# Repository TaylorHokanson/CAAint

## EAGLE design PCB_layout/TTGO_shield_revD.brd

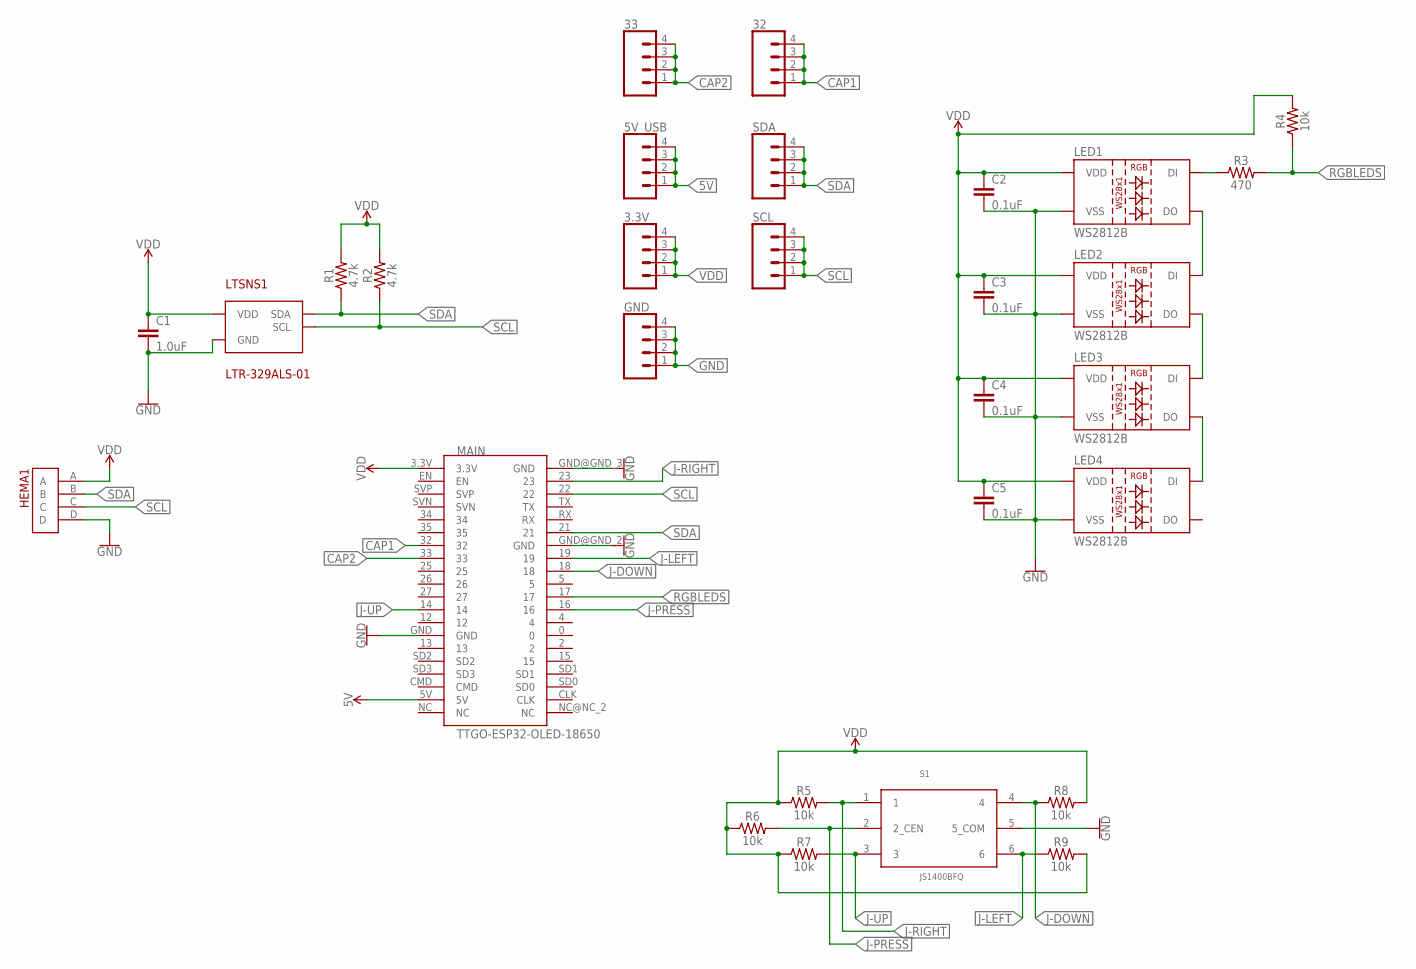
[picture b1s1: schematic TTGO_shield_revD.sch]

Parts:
3.3V, 5V_USB, 32, 33: CONN_041X04_NO_SILK; 1X04_NO_SILK
C1: 1.0uF; 0805
C2, C3, C4, C5: 0.1uF; 0603
GND: CONN_041X04_NO_SILK; 1X04_NO_SILK
HEMA1: 10120045-400LF
LED1, LED2, LED3, LED4: WS2812B
LTSNS1: LTR-329ALS-01; CHIPLED-4
MAIN: TTGO-ESP32-OLED-18650
R1, R2: 4.7k; 0603
R3: 470; 0603
R4, R5, R6, R7, R8, R9: 10k; 0603
S1: JS1400BFQ
SCL: CONN_041X04_NO_SILK; 1X04_NO_SILK
SDA: CONN_041X04_NO_SILK; 1X04_NO_SILK

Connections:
5V: 5V_USB.1, 5V_USB.2, 5V_USB.3, 5V_USB.4, MAIN.5V
CAP1: 32.1, 32.2, 32.3, 32.4, MAIN.32
CAP2: 33.1, 33.2, 33.3, 33.4, MAIN.33
GND: C1.2, C2.2, C3.2, C4.2, C5.2, GND.1, GND.2, GND.3, GND.4, HEMA1.D, LED1.3 (VSS), LED2.3 (VSS), LED3.3 (VSS), LED4.3 (VSS), LTSNS1.2 (GND), MAIN.GND, MAIN.GND@GND_2 (GND), MAIN.GND@GND_3 (GND), S1.5 (5_COM)
J-DOWN: MAIN.18, R8.1, S1.4
J-LEFT: MAIN.19, R9.1, S1.6
J-PRESS: MAIN.16, R6.2, S1.2 (2_CEN)
J-RIGHT: MAIN.23, R5.2, S1.1
J-UP: MAIN.14, R7.2, S1.3
unnamed: LED1.2 (DO), LED2.4 (DI)
unnamed: LED2.2 (DO), LED3.4 (DI)
unnamed: LED3.2 (DO), LED4.4 (DI)
unnamed: LED1.4 (DI), R3.1
RGBLEDS: MAIN.17, R3.2, R4.1
SCL: HEMA1.C, LTSNS1.4 (SCL), MAIN.22, R2.1, SCL.1, SCL.2, SCL.3, SCL.4
SDA: HEMA1.B, LTSNS1.3 (SDA), MAIN.21, R1.1, SDA.1, SDA.2, SDA.3, SDA.4
VDD: 3.3V.1, 3.3V.2, 3.3V.3, 3.3V.4, C1.1, C2.1, C3.1, C4.1, C5.1, HEMA1.A, LED1.1 (VDD), LED2.1 (VDD), LED3.1 (VDD), LED4.1 (VDD), LTSNS1.1 (VDD), MAIN.3.3V, R1.2, R2.2, R4.2, R5.1, R6.1, R7.1, R8.2, R9.2

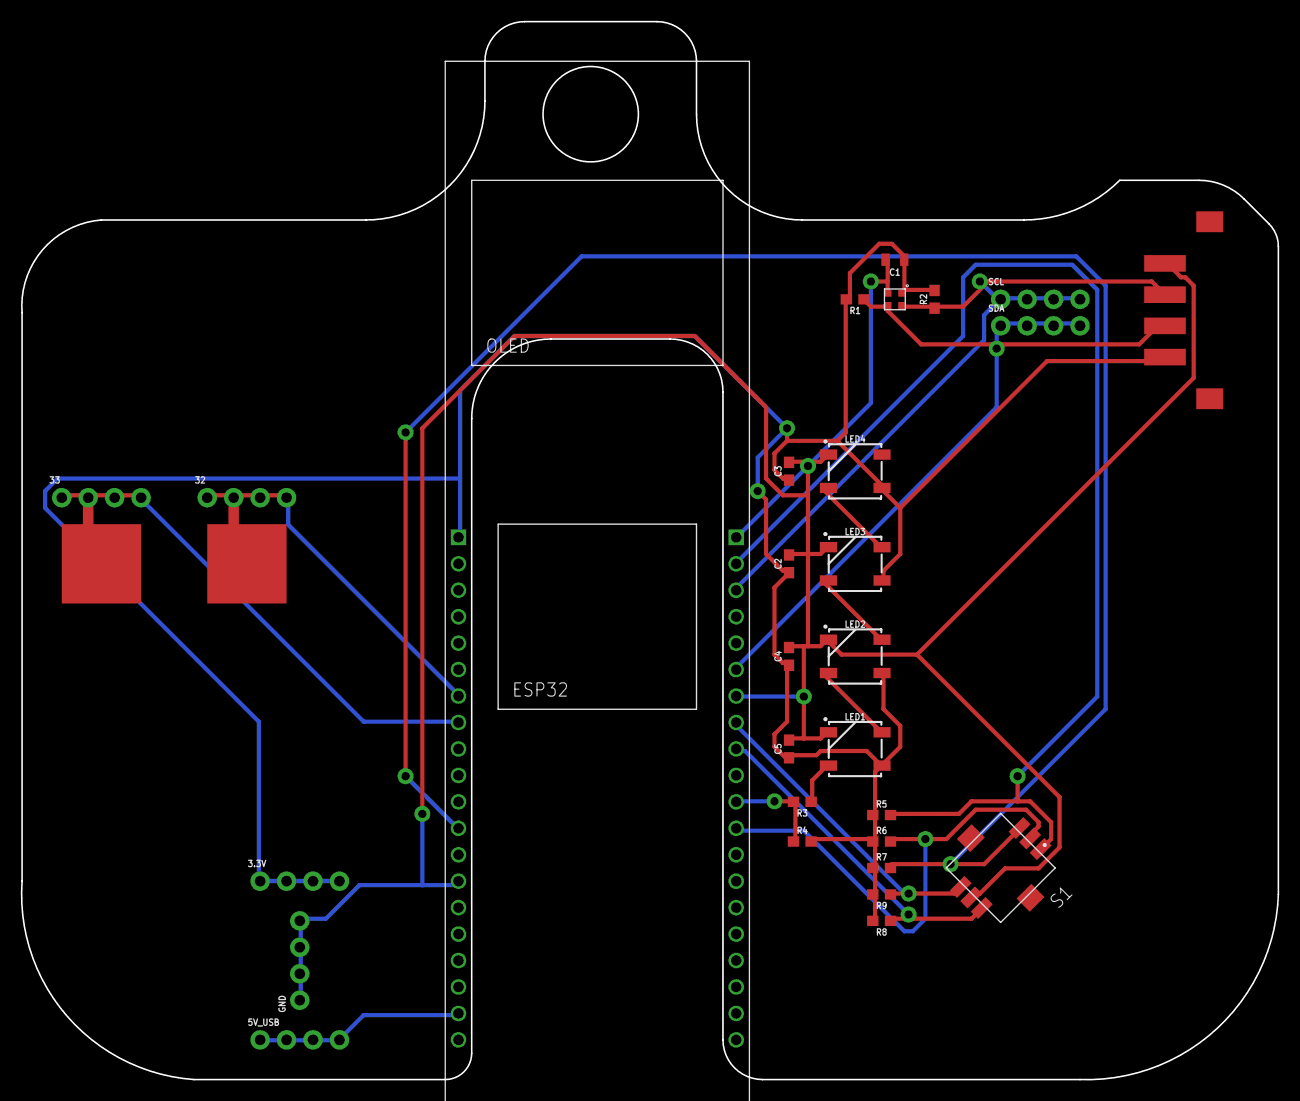
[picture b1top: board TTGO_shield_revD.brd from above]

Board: 2 copper layers, 120.7 x 101.6 mm, 29 parts (0 on the bottom side), 17 nets.

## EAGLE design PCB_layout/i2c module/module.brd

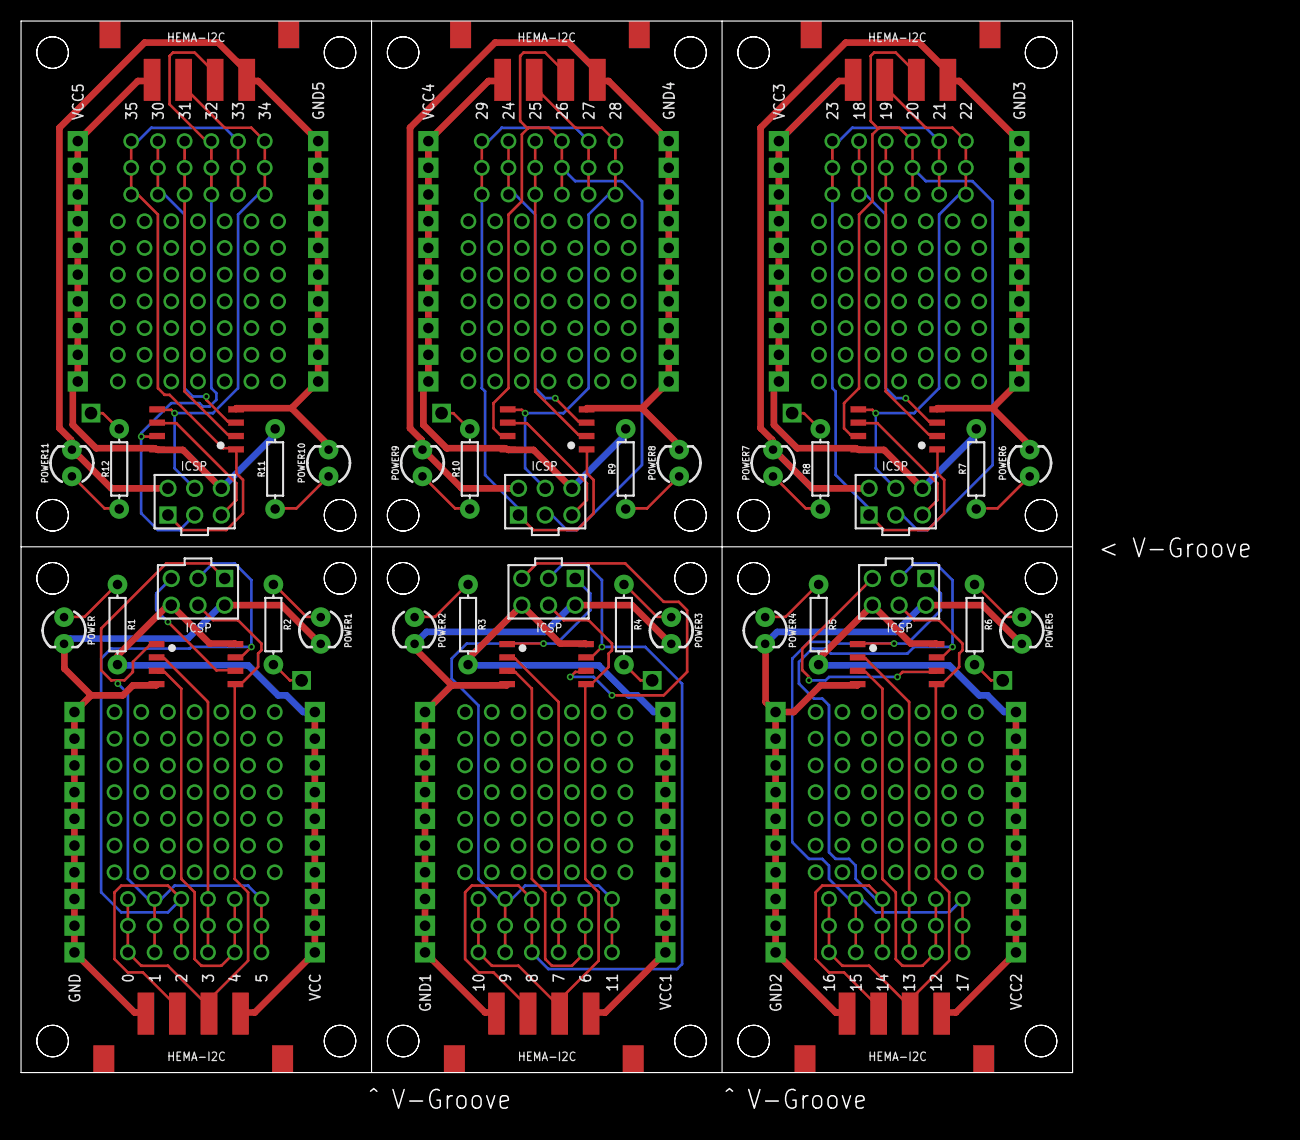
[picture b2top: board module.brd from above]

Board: 2 copper layers, 100.0 x 100.0 mm, 102 parts (0 on the bottom side), 66 nets.

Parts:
0, 1, 2, 3, 4, 5, 6, 7, 8, 9, 10, 11, 12, 13, 14, 15, 16, 17, 18, 19, 20, 21, 22, 23, 24, 25, 26, 27, 28, 29, 30, 31, 32, 33, 34, 35: 3X-PADS-CONNECTED; 3X-PADS
GND, GND1, GND2, GND3, GND4, GND5: 10X-PADS
IC1, IC2, IC3, IC4, IC5, IC6: ATTINY85-20SU; SOT127P798X216-8N
J1, J2, J3, J4, J5, J6: M20-9980346; HDRV6W64P254_2X3_762X508X868P
P1, P2, P3, P4, P5, P6: PROTO_VIAS_01X01-1.2; PROTO_VIAS_01X01_1.2
POWER, POWER1, POWER2, POWER3, POWER4, POWER5, POWER6, POWER7, POWER8, POWER9, POWER10, POWER11: LED_3MM
R1, R2, R3, R4, R5, R6, R7, R8, R9, R10, R11, R12: 220; AXIAL-0.3
U$1, U$3, U$5, U$7, U$9, U$11: HEMA-I2C
U$2, U$4, U$6, U$8, U$10, U$12: 7X-PADS-NC
VCC, VCC1, VCC2, VCC3, VCC4, VCC5: 10X-PADS

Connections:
GND: GND.P$1, GND.P$2, GND.P$3, GND.P$4, GND.P$5, GND.P$6, GND.P$7, GND.P$8, GND.P$9, GND.P$10, IC1.GND, J1.GND, POWER.K, POWER1.K, U$1.A
GND1: GND1.P$1, GND1.P$2, GND1.P$3, GND1.P$4, GND1.P$5, GND1.P$6, GND1.P$7, GND1.P$8, GND1.P$9, GND1.P$10, IC2.GND, J2.GND, POWER2.K, POWER3.K, U$3.A
GND2: GND2.P$1, GND2.P$2, GND2.P$3, GND2.P$4, GND2.P$5, GND2.P$6, GND2.P$7, GND2.P$8, GND2.P$9, GND2.P$10, IC3.GND, J3.GND, POWER4.K, POWER5.K, U$5.A
GND3: GND3.P$1, GND3.P$2, GND3.P$3, GND3.P$4, GND3.P$5, GND3.P$6, GND3.P$7, GND3.P$8, GND3.P$9, GND3.P$10, IC4.GND, J4.GND, POWER6.K, POWER7.K, U$7.A
GND4: GND4.P$1, GND4.P$2, GND4.P$3, GND4.P$4, GND4.P$5, GND4.P$6, GND4.P$7, GND4.P$8, GND4.P$9, GND4.P$10, IC5.GND, J5.GND, POWER8.K, POWER9.K, U$9.A
GND5: GND5.P$1, GND5.P$2, GND5.P$3, GND5.P$4, GND5.P$5, GND5.P$6, GND5.P$7, GND5.P$8, GND5.P$9, GND5.P$10, IC6.GND, J6.GND, POWER10.K, POWER11.K, U$11.A
unnamed: POWER1.A, R2.P$1
unnamed: P1.1, R2.P$2
unnamed: POWER2.A, R3.P$1
unnamed: POWER3.A, R4.P$1
unnamed: P2.1, R4.P$2
unnamed: POWER4.A, R5.P$1
unnamed: POWER5.A, R6.P$1
unnamed: P3.1, R6.P$2
unnamed: POWER6.A, R7.P$1
unnamed: POWER7.A, R8.P$1
unnamed: POWER.A, R1.P$1
unnamed: P4.1, R8.P$2
unnamed: POWER8.A, R9.P$1
unnamed: POWER9.A, R10.P$1
unnamed: P5.1, R10.P$2
unnamed: POWER10.A, R11.P$1
unnamed: POWER11.A, R12.P$1
unnamed: P6.1, R12.P$2
PB0: 0.P$1, 0.P$2, 0.P$3, IC1.PB0, J1.PB0, U$1.C
PB1: IC1.PB1, J1.PB1
PB2: 2.P$1, 2.P$2, 2.P$3, IC1.PB2, J1.PB2, U$1.B
PB3: 3.P$1, 3.P$2, 3.P$3, IC1.PB3
PB4: 4.P$1, 4.P$2, 4.P$3, IC1.PB4
PB5: 1.P$1, 1.P$2, 1.P$3, 5.P$1, 5.P$2, 5.P$3, IC1.PB5, J1.PB5
PB6: 10.P$1, 10.P$2, 10.P$3, IC2.PB0, J2.PB0, U$3.C
PB7: 7.P$1, 7.P$2, 7.P$3, IC2.PB3
PB8: 6.P$1, 6.P$2, 6.P$3, IC2.PB4
PB9: 8.P$1, 8.P$2, 8.P$3, IC2.PB2, J2.PB2, U$3.B
PB10: 9.P$1, 9.P$2, 9.P$3, 11.P$1, 11.P$2, 11.P$3, IC2.PB5, J2.PB5
PB11: IC2.PB1, J2.PB1
PB12: 16.P$1, 16.P$2, 16.P$3, IC3.PB0, J3.PB0, U$5.C
PB13: 13.P$1, 13.P$2, 13.P$3, IC3.PB3
PB14: 12.P$1, 12.P$2, 12.P$3, IC3.PB4
PB15: 14.P$1, 14.P$2, 14.P$3, IC3.PB2, J3.PB2, U$5.B
PB16: 15.P$1, 15.P$2, 15.P$3, 17.P$1, 17.P$2, 17.P$3, IC3.PB5, J3.PB5
PB17: IC3.PB1, J3.PB1
PB18: 22.P$1, 22.P$2, 22.P$3, IC4.PB0, J4.PB0, U$7.C
PB19: 19.P$1, 19.P$2, 19.P$3, IC4.PB3
PB20: 18.P$1, 18.P$2, 18.P$3, IC4.PB4
PB21: 20.P$1, 20.P$2, 20.P$3, IC4.PB2, J4.PB2, U$7.B
PB22: 21.P$1, 21.P$2, 21.P$3, 23.P$1, 23.P$2, 23.P$3, IC4.PB5, J4.PB5
PB23: IC4.PB1, J4.PB1
PB24: 28.P$1, 28.P$2, 28.P$3, IC5.PB0, J5.PB0, U$9.C
PB25: 25.P$1, 25.P$2, 25.P$3, IC5.PB3
PB26: 24.P$1, 24.P$2, 24.P$3, IC5.PB4
PB27: 26.P$1, 26.P$2, 26.P$3, IC5.PB2, J5.PB2, U$9.B
PB28: 27.P$1, 27.P$2, 27.P$3, 29.P$1, 29.P$2, 29.P$3, IC5.PB5, J5.PB5
PB29: IC5.PB1, J5.PB1
PB30: 34.P$1, 34.P$2, 34.P$3, IC6.PB0, J6.PB0, U$11.C
PB31: 31.P$1, 31.P$2, 31.P$3, IC6.PB3
PB32: 30.P$1, 30.P$2, 30.P$3, IC6.PB4
PB33: 32.P$1, 32.P$2, 32.P$3, IC6.PB2, J6.PB2, U$11.B
PB34: 33.P$1, 33.P$2, 33.P$3, 35.P$1, 35.P$2, 35.P$3, IC6.PB5, J6.PB5
PB35: IC6.PB1, J6.PB1
VCC: IC1.VCC, J1.VCC, R1.P$2, U$1.D, VCC.P$1, VCC.P$2, VCC.P$3, VCC.P$4, VCC.P$5, VCC.P$6, VCC.P$7, VCC.P$8, VCC.P$9, VCC.P$10
VCC1: IC2.VCC, J2.VCC, R3.P$2, U$3.D, VCC1.P$1, VCC1.P$2, VCC1.P$3, VCC1.P$4, VCC1.P$5, VCC1.P$6, VCC1.P$7, VCC1.P$8, VCC1.P$9, VCC1.P$10
VCC2: IC3.VCC, J3.VCC, R5.P$2, U$5.D, VCC2.P$1, VCC2.P$2, VCC2.P$3, VCC2.P$4, VCC2.P$5, VCC2.P$6, VCC2.P$7, VCC2.P$8, VCC2.P$9, VCC2.P$10
VCC3: IC4.VCC, J4.VCC, R7.P$2, U$7.D, VCC3.P$1, VCC3.P$2, VCC3.P$3, VCC3.P$4, VCC3.P$5, VCC3.P$6, VCC3.P$7, VCC3.P$8, VCC3.P$9, VCC3.P$10
VCC4: IC5.VCC, J5.VCC, R9.P$2, U$9.D, VCC4.P$1, VCC4.P$2, VCC4.P$3, VCC4.P$4, VCC4.P$5, VCC4.P$6, VCC4.P$7, VCC4.P$8, VCC4.P$9, VCC4.P$10
VCC5: IC6.VCC, J6.VCC, R11.P$2, U$11.D, VCC5.P$1, VCC5.P$2, VCC5.P$3, VCC5.P$4, VCC5.P$5, VCC5.P$6, VCC5.P$7, VCC5.P$8, VCC5.P$9, VCC5.P$10

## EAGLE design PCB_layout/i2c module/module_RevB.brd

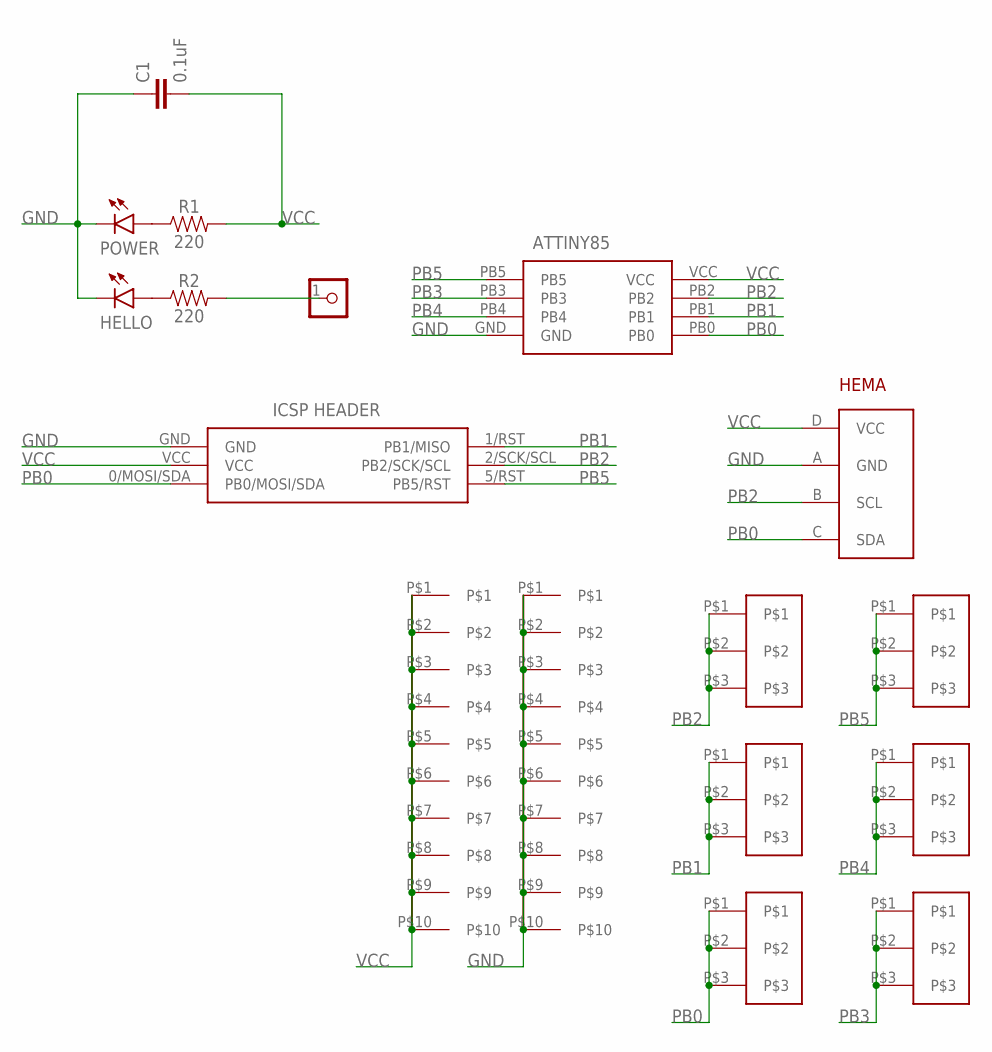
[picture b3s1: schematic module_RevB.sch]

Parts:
0, 1, 2, 3, 4, 5: 3X-PADS-CONNECTED; 3X-PADS
C1: 0.1uF; 0603
GND: 10X-PADS
HELLO: LED3MM
IC1: ATTINY85-20SU; SOT127P798X216-8N
J1: M20-9980346; HDRV6W64P254_2X3_762X508X868P
P1: PROTO_VIAS_01X01-1.2; PROTO_VIAS_01X01_1.2
POWER: LED3MM
R1, R2: 220; AXIAL-0.3
U$1: HEMA-I2C
VCC: 10X-PADS

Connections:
GND: C1.1, GND.P$1, GND.P$2, GND.P$3, GND.P$4, GND.P$5, GND.P$6, GND.P$7, GND.P$8, GND.P$9, GND.P$10, HELLO.NEG, IC1.GND, J1.GND, POWER.NEG, U$1.A (GND)
unnamed: POWER.POS, R1.P$1 (1)
unnamed: P1.1, R2.P$2 (2)
unnamed: HELLO.POS, R2.P$1 (1)
PB0: 0.P$1, 0.P$2, 0.P$3, IC1.PB0, J1.0/MOSI/SDA (PB0/MOSI/SDA), U$1.C (SDA)
PB1: 1.P$1, 1.P$2, 1.P$3, IC1.PB1, J1.1/RST (PB1/MISO)
PB2: 2.P$1, 2.P$2, 2.P$3, IC1.PB2, J1.2/SCK/SCL (PB2/SCK/SCL), U$1.B (SCL)
PB3: 3.P$1, 3.P$2, 3.P$3, IC1.PB3
PB4: 4.P$1, 4.P$2, 4.P$3, IC1.PB4
PB5: 5.P$1, 5.P$2, 5.P$3, IC1.PB5, J1.5/RST (PB5/RST)
VCC: C1.2, IC1.VCC, J1.VCC, R1.P$2 (2), U$1.D (VCC), VCC.P$1, VCC.P$2, VCC.P$3, VCC.P$4, VCC.P$5, VCC.P$6, VCC.P$7, VCC.P$8, VCC.P$9, VCC.P$10

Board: 2 copper layers, 18 parts (0 on the bottom side), 11 nets, no tracks yet.

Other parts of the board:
U$2: 7X-PADS-NC

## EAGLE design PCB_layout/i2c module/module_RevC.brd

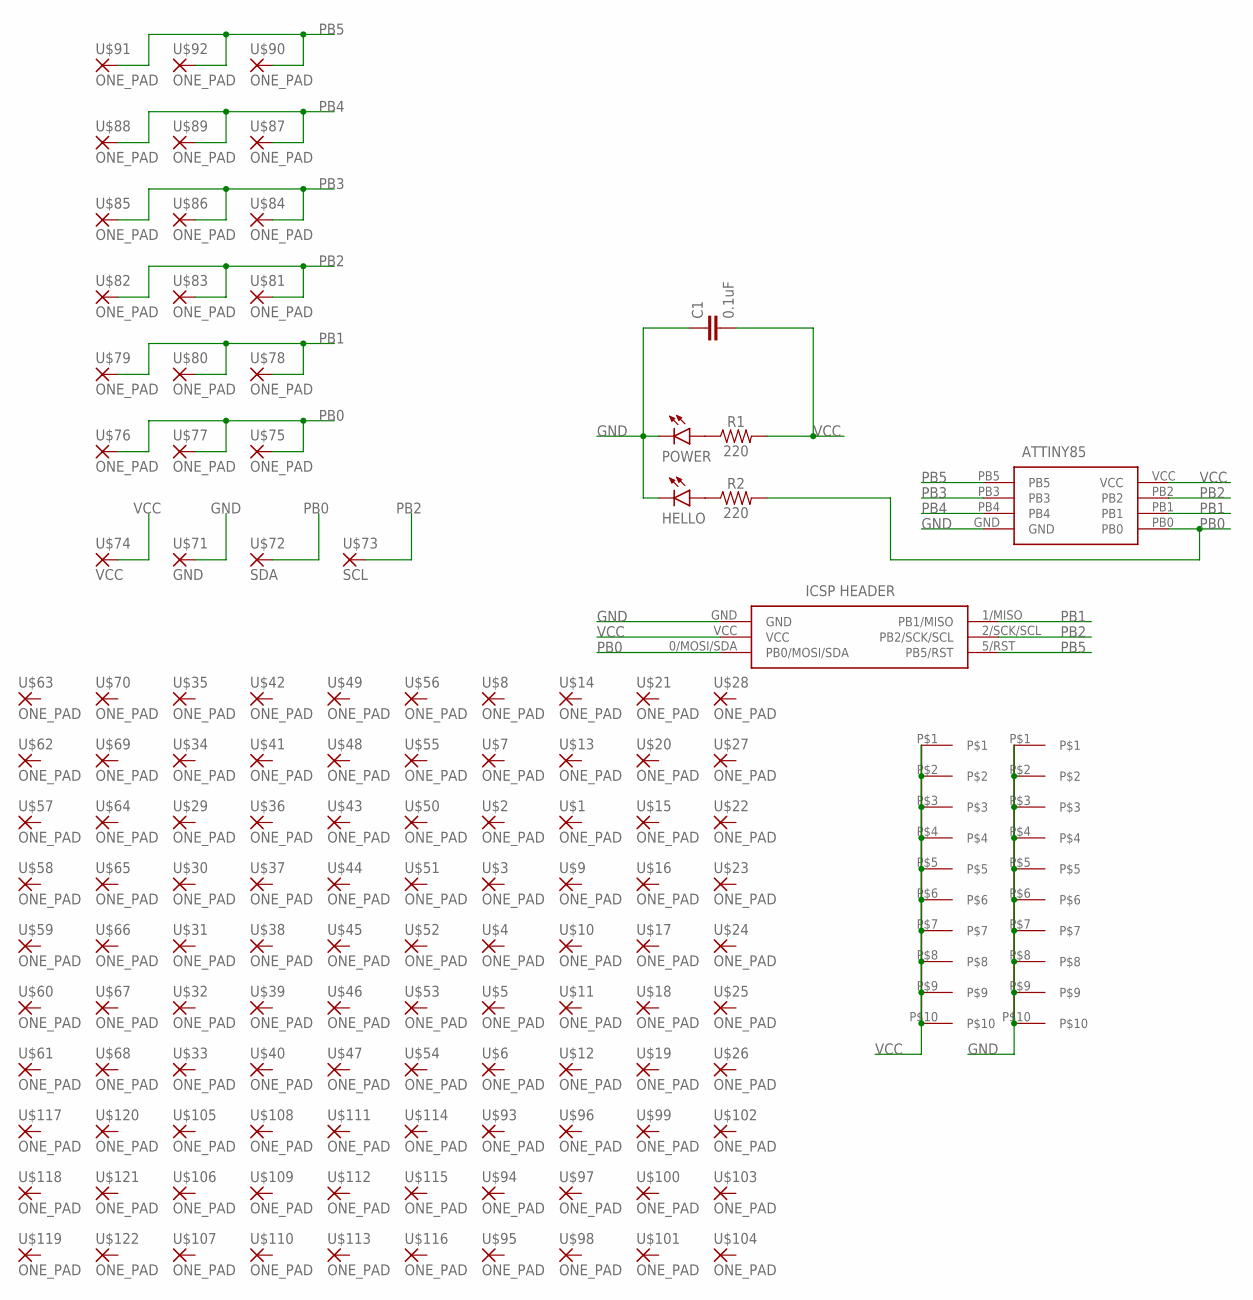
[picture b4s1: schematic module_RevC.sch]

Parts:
C1: 0.1uF; 0603
GND: 10X-PADS
HELLO: LED3MM
IC1: ATTINY85-20SU; SOT127P798X216-8N
J1: M20-9980346; HDRV6W64P254_2X3_762X508X868P
POWER: LED3MM
R1, R2: 220; AXIAL-0.3
U$1, U$2, U$3, U$4, U$5, U$6, U$7, U$8, U$9, U$10, U$11, U$12, U$13, U$14, U$15, U$16, U$17, U$18, U$19, U$20, U$21, U$22, U$23, U$24, U$25, U$26, U$27, U$28, U$29, U$30, U$31, U$32, U$33, U$34, U$35, U$36, U$37, U$38, U$39, U$40, U$41, U$42, U$43, U$44, U$45, U$46, U$47, U$48, U$49, U$50, U$51, U$52, U$53, U$54, U$55, U$56, U$57, U$58, U$59, U$60, U$61, U$62, U$63, U$64, U$65, U$66, U$67, U$68, U$69, U$70, U$75, U$76, U$77, U$78, U$79, U$80, U$81, U$82, U$83, U$84, U$85, U$86, U$87, U$88, U$89, U$90, U$91, U$92, U$93, U$94, U$95, U$96, U$97, U$98, U$99, U$100, U$101, U$102, U$103, U$104, U$105, U$106, U$107, U$108, U$109, U$110, U$111, U$112, U$113, U$114, U$115, U$116, U$117, U$118, U$119, U$120, U$121, U$122: ONE_PAD; 1X01
U$71: GND; 1X01
U$72: SDA; 1X01
U$73: SCL; 1X01
U$74: VCC; 1X01
VCC: 10X-PADS

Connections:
GND: C1.1, GND.P$1, GND.P$2, GND.P$3, GND.P$4, GND.P$5, GND.P$6, GND.P$7, GND.P$8, GND.P$9, GND.P$10, HELLO.NEG, IC1.GND, J1.GND, POWER.NEG, U$71.1
unnamed: POWER.POS, R1.P$1 (1)
unnamed: HELLO.POS, R2.P$1 (1)
PB0: IC1.PB0, J1.0/MOSI/SDA (PB0/MOSI/SDA), R2.P$2 (2), U$72.1, U$75.1, U$76.1, U$77.1
PB1: IC1.PB1, J1.1/MISO (PB1/MISO), U$78.1, U$79.1, U$80.1
PB2: IC1.PB2, J1.2/SCK/SCL (PB2/SCK/SCL), U$73.1, U$81.1, U$82.1, U$83.1
PB3: IC1.PB3, U$84.1, U$85.1, U$86.1
PB4: IC1.PB4, U$87.1, U$88.1, U$89.1
PB5: IC1.PB5, J1.5/RST (PB5/RST), U$90.1, U$91.1, U$92.1
VCC: C1.2, IC1.VCC, J1.VCC, R1.P$2 (2), U$74.1, VCC.P$1, VCC.P$2, VCC.P$3, VCC.P$4, VCC.P$5, VCC.P$6, VCC.P$7, VCC.P$8, VCC.P$9, VCC.P$10

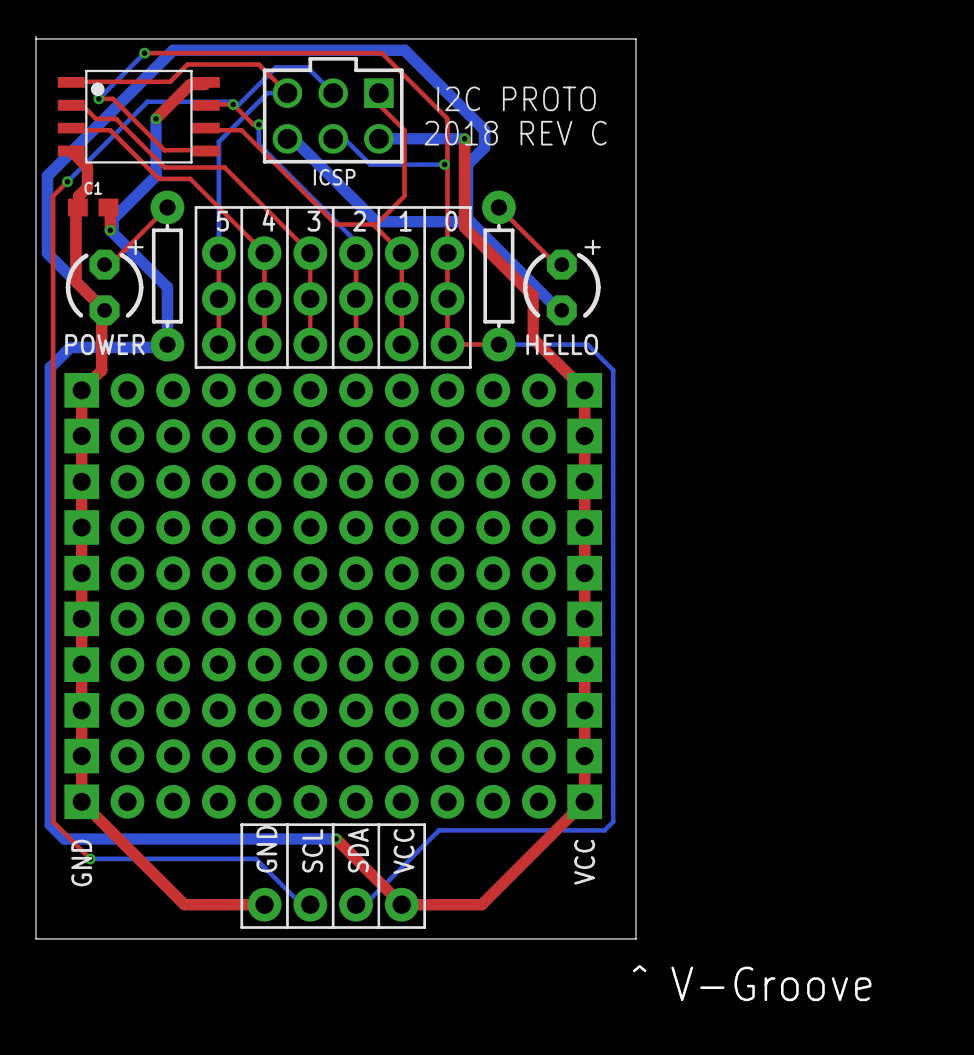
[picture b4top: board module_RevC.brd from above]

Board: 2 copper layers, 33.3 x 50.2 mm, 131 parts (0 on the bottom side), 10 nets.

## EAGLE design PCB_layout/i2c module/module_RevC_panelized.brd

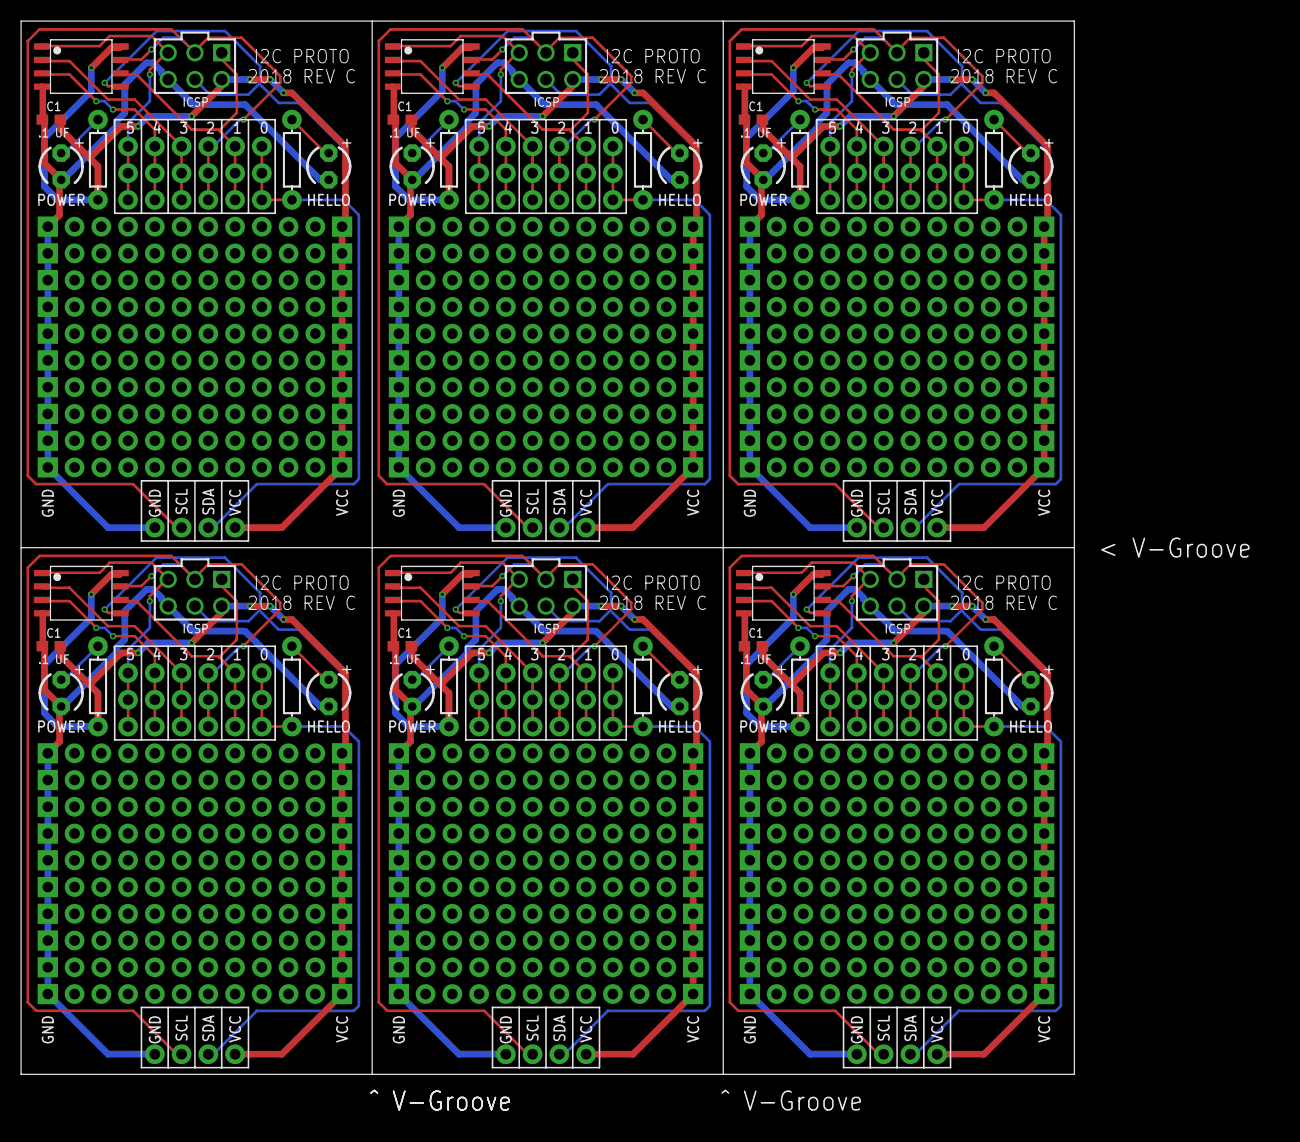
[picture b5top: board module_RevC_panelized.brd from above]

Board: 2 copper layers, 100.0 x 100.0 mm, 786 parts (0 on the bottom side), 60 nets.

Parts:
C1, C2, C3, C4, C5, C6: 0.1uF; 0603
GND, GND1, GND2, GND3, GND4, GND5: 10X-PADS
HELLO, HELLO1, HELLO2, HELLO3, HELLO4, HELLO5: LED3MM
IC1, IC2, IC3, IC4, IC5, IC6: ATTINY85-20SU; SOT127P798X216-8N
J1, J2, J3, J4, J5, J6: M20-9980346; HDRV6W64P254_2X3_762X508X868P
POWER, POWER1, POWER2, POWER3, POWER4, POWER5: LED3MM
R1, R2, R3, R4, R5, R6, R7, R8, R9, R10, R11, R12: 220; AXIAL-0.3
U$1, U$2, U$3, U$4, U$5, U$6, U$7, U$8, U$9, U$10, U$11, U$12, U$13, U$14, U$15, U$16, U$17, U$18, U$19, U$20, U$21, U$22, U$23, U$24, U$25, U$26, U$27, U$28, U$29, U$30, U$31, U$32, U$33, U$34, U$35, U$36, U$37, U$38, U$39, U$40, U$41, U$42, U$43, U$44, U$45, U$46, U$47, U$48, U$49, U$50, U$51, U$52, U$53, U$54, U$55, U$56, U$57, U$58, U$59, U$60, U$61, U$62, U$63, U$64, U$65, U$66, U$67, U$68, U$69, U$70, U$75, U$76, U$77, U$78, U$79, U$80, U$81, U$82, U$83, U$84, U$85, U$86, U$87, U$88, U$89, U$90, U$91, U$92, U$93, U$94, U$95, U$96, U$97, U$98, U$99, U$100, U$101, U$102, U$103, U$104, U$105, U$106, U$107, U$108, U$109, U$110, U$111, U$112, U$113, U$114, U$115, U$116, U$117, U$118, U$119, U$120, U$121, U$122, U$123, U$124, U$125, U$126, U$127, U$128, U$129, U$130, U$131, U$132, U$133, U$134, U$135, U$136, U$137, U$138, U$139, U$140, U$141, U$142, U$143, U$144, U$145, U$146, U$147, U$148, U$149, U$150, U$151, U$152, U$153, U$154, U$155, U$156, U$157, U$158, U$159, U$160, U$161, U$162, U$163, U$164, U$165, U$166, U$167, U$168, U$169, U$170, U$171, U$172, U$173, U$174, U$175, U$176, U$177, U$178, U$179, U$180, U$181, U$182, U$183, U$184, U$185, U$186, U$187, U$188, U$189, U$190, U$191, U$192, U$197, U$198, U$199, U$200, U$201, U$202, U$203, U$204, U$205, U$206, U$207, U$208, U$209, U$210, U$211, U$212, U$213, U$214, U$215, U$216, U$217, U$218, U$219, U$220, U$221, U$222, U$223, U$224, U$225, U$226, U$227, U$228, U$229, U$230, U$231, U$232, U$233, U$234, U$235, U$236, U$237, U$238, U$239, U$240, U$241, U$242, U$243, U$244, U$245, U$246, U$247, U$248, U$249, U$250, U$251, U$252, U$253, U$254, U$255, U$256, U$257, U$258, U$259, U$260, U$261, U$262, U$263, U$264, U$265, U$266, U$267, U$268, U$269, U$270, U$271, U$272, U$273, U$274, U$275, U$276, U$277, U$278, U$279, U$280, U$281, U$282, U$283, U$284, U$285, U$286, U$287, U$288, U$289, U$290, U$291, U$292, U$293, U$294, U$295, U$296, U$297, U$298, U$299, U$300, U$301, U$302, U$303, U$304, U$305, U$306, U$307, U$308, U$309, U$310, U$311, U$312, U$313, U$314, U$319, U$320, U$321, U$322, U$323, U$324, U$325, U$326, U$327, U$328, U$329, U$330, U$331, U$332, U$333, U$334, U$335, U$336, U$337, U$338, U$339, U$340, U$341, U$342, U$343, U$344, U$345, U$346, U$347, U$348, U$349, U$350, U$351, U$352, U$353, U$354, U$355, U$356, U$357, U$358, U$359, U$360, U$361, U$362, U$363, U$364, U$365, U$366, U$367, U$368, U$369, U$370, U$371, U$372, U$373, U$374, U$375, U$376, U$377, U$378, U$379, U$380, U$381, U$382, U$383, U$384, U$385, U$386, U$387, U$388, U$389, U$390, U$391, U$392, U$393, U$394, U$395, U$396, U$397, U$398, U$399, U$400, U$401, U$402, U$403, U$404, U$405, U$406, U$407, U$408, U$409, U$410, U$411, U$412, U$413, U$414, U$415, U$416, U$417, U$418, U$419, U$420, U$421, U$422, U$423, U$424, U$425, U$426, U$427, U$428, U$429, U$430, U$431, U$432, U$433, U$434, U$435, U$436, U$441, U$442, U$443, U$444, U$445, U$446, U$447, U$448, U$449, U$450, U$451, U$452, U$453, U$454, U$455, U$456, U$457, U$458, U$459, U$460, U$461, U$462, U$463, U$464, U$465, U$466, U$467, U$468, U$469, U$470, U$471, U$472, U$473, U$474, U$475, U$476, U$477, U$478, U$479, U$480, U$481, U$482, U$483, U$484, U$485, U$486, U$487, U$488, U$489, U$490, U$491, U$492, U$493, U$494, U$495, U$496, U$497, U$498, U$499, U$500, U$501, U$502, U$503, U$504, U$505, U$506, U$507, U$508, U$509, U$510, U$511, U$512, U$513, U$514, U$515, U$516, U$517, U$518, U$519, U$520, U$521, U$522, U$523, U$524, U$525, U$526, U$527, U$528, U$529, U$530, U$531, U$532, U$533, U$534, U$535, U$536, U$537, U$538, U$539, U$540, U$541, U$542, U$543, U$544, U$545, U$546, U$547, U$548, U$549, U$550, U$551, U$552, U$553, U$554, U$555, U$556, U$557, U$558, U$563, U$564, U$565, U$566, U$567, U$568, U$569, U$570, U$571, U$572, U$573, U$574, U$575, U$576, U$577, U$578, U$579, U$580, U$581, U$582, U$583, U$584, U$585, U$586, U$587, U$588, U$589, U$590, U$591, U$592, U$593, U$594, U$595, U$596, U$597, U$598, U$599, U$600, U$601, U$602, U$603, U$604, U$605, U$606, U$607, U$608, U$609, U$610, U$611, U$612, U$613, U$614, U$615, U$616, U$617, U$618, U$619, U$620, U$621, U$622, U$623, U$624, U$625, U$626, U$627, U$628, U$629, U$630, U$631, U$632, U$633, U$634, U$635, U$636, U$637, U$638, U$639, U$640, U$641, U$642, U$643, U$644, U$645, U$646, U$647, U$648, U$649, U$650, U$651, U$652, U$653, U$654, U$655, U$656, U$657, U$658, U$659, U$660, U$661, U$662, U$663, U$664, U$665, U$666, U$667, U$668, U$669, U$670, U$671, U$672, U$673, U$674, U$675, U$676, U$677, U$678, U$679, U$680, U$685, U$686, U$687, U$688, U$689, U$690, U$691, U$692, U$693, U$694, U$695, U$696, U$697, U$698, U$699, U$700, U$701, U$702, U$703, U$704, U$705, U$706, U$707, U$708, U$709, U$710, U$711, U$712, U$713, U$714, U$715, U$716, U$717, U$718, U$719, U$720, U$721, U$722, U$723, U$724, U$725, U$726, U$727, U$728, U$729, U$730, U$731, U$732: ONE_PAD; 1X01
U$71, U$193, U$315, U$437, U$559, U$681: GND; 1X01
U$72, U$195, U$317, U$439, U$561, U$683: SDA; 1X01
U$73, U$196, U$318, U$440, U$562, U$684: SCL; 1X01
U$74, U$194, U$316, U$438, U$560, U$682: VCC; 1X01
VCC, VCC1, VCC2, VCC3, VCC4, VCC5: 10X-PADS

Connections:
GND: C1.1, GND.P$1, GND.P$2, GND.P$3, GND.P$4, GND.P$5, GND.P$6, GND.P$7, GND.P$8, GND.P$9, GND.P$10, HELLO.NEG, IC1.GND, J1.GND, POWER.NEG, U$71.1
GND1: C2.1, GND1.P$1, GND1.P$2, GND1.P$3, GND1.P$4, GND1.P$5, GND1.P$6, GND1.P$7, GND1.P$8, GND1.P$9, GND1.P$10, HELLO1.NEG, IC2.GND, J2.GND, POWER1.NEG, U$193.1
GND2: C3.1, GND2.P$1, GND2.P$2, GND2.P$3, GND2.P$4, GND2.P$5, GND2.P$6, GND2.P$7, GND2.P$8, GND2.P$9, GND2.P$10, HELLO2.NEG, IC3.GND, J3.GND, POWER2.NEG, U$315.1
GND3: C4.1, GND3.P$1, GND3.P$2, GND3.P$3, GND3.P$4, GND3.P$5, GND3.P$6, GND3.P$7, GND3.P$8, GND3.P$9, GND3.P$10, HELLO3.NEG, IC4.GND, J4.GND, POWER3.NEG, U$437.1
GND4: C5.1, GND4.P$1, GND4.P$2, GND4.P$3, GND4.P$4, GND4.P$5, GND4.P$6, GND4.P$7, GND4.P$8, GND4.P$9, GND4.P$10, HELLO4.NEG, IC5.GND, J5.GND, POWER4.NEG, U$559.1
GND5: C6.1, GND5.P$1, GND5.P$2, GND5.P$3, GND5.P$4, GND5.P$5, GND5.P$6, GND5.P$7, GND5.P$8, GND5.P$9, GND5.P$10, HELLO5.NEG, IC6.GND, J6.GND, POWER5.NEG, U$681.1
unnamed: POWER.POS, R1.P$1
unnamed: POWER1.POS, R3.P$1
unnamed: HELLO.POS, R2.P$1
unnamed: HELLO1.POS, R4.P$1
unnamed: POWER2.POS, R5.P$1
unnamed: HELLO2.POS, R6.P$1
unnamed: POWER3.POS, R7.P$1
unnamed: HELLO3.POS, R8.P$1
unnamed: POWER4.POS, R9.P$1
unnamed: HELLO4.POS, R10.P$1
unnamed: POWER5.POS, R11.P$1
unnamed: HELLO5.POS, R12.P$1
PB0: IC1.PB0, J1.0/MOSI/SDA, R2.P$2, U$72.1, U$75.1, U$76.1, U$77.1
PB1: IC1.PB1, J1.1/MISO, U$78.1, U$79.1, U$80.1
PB2: IC1.PB2, J1.2/SCK/SCL, U$73.1, U$81.1, U$82.1, U$83.1
PB3: IC1.PB3, U$84.1, U$85.1, U$86.1
PB4: IC1.PB4, U$87.1, U$88.1, U$89.1
PB5: IC1.PB5, J1.5/RST, U$90.1, U$91.1, U$92.1
PB6: IC2.PB0, J2.0/MOSI/SDA, R4.P$2, U$195.1, U$197.1, U$198.1, U$199.1
PB7: IC2.PB3, U$206.1, U$207.1, U$208.1
PB8: IC2.PB4, U$209.1, U$210.1, U$211.1
PB9: IC2.PB2, J2.2/SCK/SCL, U$196.1, U$203.1, U$204.1, U$205.1
PB10: IC2.PB5, J2.5/RST, U$212.1, U$213.1, U$214.1
PB11: IC2.PB1, J2.1/MISO, U$200.1, U$201.1, U$202.1
PB12: IC3.PB0, J3.0/MOSI/SDA, R6.P$2, U$317.1, U$319.1, U$320.1, U$321.1
PB13: IC3.PB3, U$328.1, U$329.1, U$330.1
PB14: IC3.PB4, U$331.1, U$332.1, U$333.1
PB15: IC3.PB2, J3.2/SCK/SCL, U$318.1, U$325.1, U$326.1, U$327.1
PB16: IC3.PB5, J3.5/RST, U$334.1, U$335.1, U$336.1
PB17: IC3.PB1, J3.1/MISO, U$322.1, U$323.1, U$324.1
PB18: IC4.PB0, J4.0/MOSI/SDA, R8.P$2, U$439.1, U$441.1, U$442.1, U$443.1
PB19: IC4.PB3, U$450.1, U$451.1, U$452.1
PB20: IC4.PB4, U$453.1, U$454.1, U$455.1
PB21: IC4.PB2, J4.2/SCK/SCL, U$440.1, U$447.1, U$448.1, U$449.1
PB22: IC4.PB5, J4.5/RST, U$456.1, U$457.1, U$458.1
PB23: IC4.PB1, J4.1/MISO, U$444.1, U$445.1, U$446.1
PB24: IC5.PB0, J5.0/MOSI/SDA, R10.P$2, U$561.1, U$563.1, U$564.1, U$565.1
PB25: IC5.PB3, U$572.1, U$573.1, U$574.1
PB26: IC5.PB4, U$575.1, U$576.1, U$577.1
PB27: IC5.PB2, J5.2/SCK/SCL, U$562.1, U$569.1, U$570.1, U$571.1
PB28: IC5.PB5, J5.5/RST, U$578.1, U$579.1, U$580.1
PB29: IC5.PB1, J5.1/MISO, U$566.1, U$567.1, U$568.1
PB30: IC6.PB0, J6.0/MOSI/SDA, R12.P$2, U$683.1, U$685.1, U$686.1, U$687.1
PB31: IC6.PB3, U$694.1, U$695.1, U$696.1
PB32: IC6.PB4, U$697.1, U$698.1, U$699.1
PB33: IC6.PB2, J6.2/SCK/SCL, U$684.1, U$691.1, U$692.1, U$693.1
PB34: IC6.PB5, J6.5/RST, U$700.1, U$701.1, U$702.1
PB35: IC6.PB1, J6.1/MISO, U$688.1, U$689.1, U$690.1
VCC: C1.2, IC1.VCC, J1.VCC, R1.P$2, U$74.1, VCC.P$1, VCC.P$2, VCC.P$3, VCC.P$4, VCC.P$5, VCC.P$6, VCC.P$7, VCC.P$8, VCC.P$9, VCC.P$10
VCC1: C2.2, IC2.VCC, J2.VCC, R3.P$2, U$194.1, VCC1.P$1, VCC1.P$2, VCC1.P$3, VCC1.P$4, VCC1.P$5, VCC1.P$6, VCC1.P$7, VCC1.P$8, VCC1.P$9, VCC1.P$10
VCC2: C3.2, IC3.VCC, J3.VCC, R5.P$2, U$316.1, VCC2.P$1, VCC2.P$2, VCC2.P$3, VCC2.P$4, VCC2.P$5, VCC2.P$6, VCC2.P$7, VCC2.P$8, VCC2.P$9, VCC2.P$10
VCC3: C4.2, IC4.VCC, J4.VCC, R7.P$2, U$438.1, VCC3.P$1, VCC3.P$2, VCC3.P$3, VCC3.P$4, VCC3.P$5, VCC3.P$6, VCC3.P$7, VCC3.P$8, VCC3.P$9, VCC3.P$10
VCC4: C5.2, IC5.VCC, J5.VCC, R9.P$2, U$560.1, VCC4.P$1, VCC4.P$2, VCC4.P$3, VCC4.P$4, VCC4.P$5, VCC4.P$6, VCC4.P$7, VCC4.P$8, VCC4.P$9, VCC4.P$10
VCC5: C6.2, IC6.VCC, J6.VCC, R11.P$2, U$682.1, VCC5.P$1, VCC5.P$2, VCC5.P$3, VCC5.P$4, VCC5.P$5, VCC5.P$6, VCC5.P$7, VCC5.P$8, VCC5.P$9, VCC5.P$10

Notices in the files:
parts and their libraries:
SparkFun-Capacitors: Licensing: Creative Commons ShareAlike 4.0 International - https://creativecommons.org/licenses/by-sa/4.0
